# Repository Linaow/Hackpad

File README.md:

# Hackpad
Mini Keypad (Four keys for four directions) with neopixels that intract with the keys
Simply, plug in the pad into your PC, voila! the external keyboard is working!
<h3>CAD:</h3>

<h3>PCB:</h3>

<h3>BOM:</h3>
<ul>
  <li>1x Seeed XIAO RP2040</li>
  <li>4x Tactile Push Buttons</li>
  <li>2x SK6812SMINI Addressable RGB LEDs</li>
</ul>

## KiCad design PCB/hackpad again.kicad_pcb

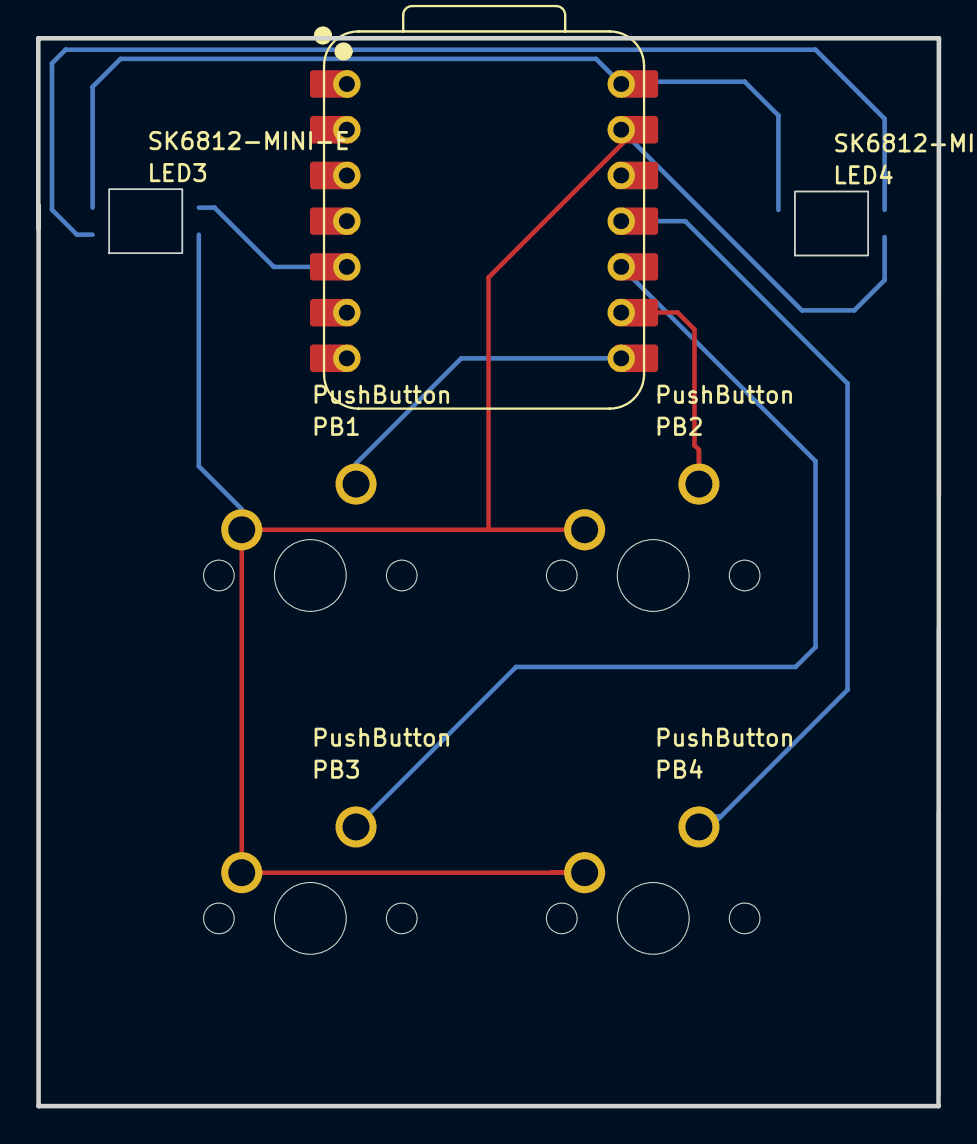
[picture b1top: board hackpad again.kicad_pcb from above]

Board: 2 copper layers, 50.0 x 59.3 mm, 7 parts (0 on the bottom side), 8 nets.

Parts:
LED3, LED4: SK6812-MINI-E; SK6812MINI-E
PB1, PB2, PB3, PB4: PushButton; MX
U1: Seeed_Studio_XIAO_Series_XIAO-RP2040-DIP; VARISTOR{colon}XIAO-RP2040-DIP

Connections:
+5V: LED3.1, LED4.1, U1.14
GND: LED3.3, LED4.3, PB1.2, PB2.2, PB3.2, PB4.2, U1.13
LED3_2: LED3.2, LED4.4
U1_5: LED3.4, U1.5
U1_8: PB1.1, U1.8
U1_9: PB2.1, U1.9
U1_10: PB3.1, U1.10
U1_11: PB4.1, U1.11

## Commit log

2026-02-04 Add files via upload
    Case 3D model, PCP & schematic diagram
2026-03-22 Update README with project description and controller info
2026-03-22 Organized the Files
2026-03-22 Update README with CAD and PCB images
    Added images and sections for CAD and PCB.
2026-03-22 Update README with more CAD images
    Added additional images for CAD section in README.
2026-03-22 Update README with more images for CAD and PCB
    Added additional images for CAD and PCB sections.
2026-03-22 Add BOM section to README
    Added BOM section with component list.
2026-03-22 Fix HTML encoding in README.md
2026-03-23 edit
2026-03-23 Replace image in README with a new one
2026-03-23 Add new PCB image to README
2026-03-23 Add new image to README and update PCB section
2026-03-23 Update PCB images in README
    Removed two images and added three new images under the PCB section.
2026-03-23 Update README with new PCB images
    Added additional PCB images to the README.
2026-03-23 Fix merge conflict in README.md
    Resolve merge conflict in README.md regarding PCB images.
